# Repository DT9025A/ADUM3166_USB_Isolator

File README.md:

# ADUM3166 USB 隔离器

**该项目使用 Kicad 进行设计，打板请使用附件中的 Gerber 文件或使用 Kicad 工程进行导出。**

使用 IS903 主控的 USB DISK 进行测试，读写速度如下：

采用 5V/5W 的隔离电源，具有较大带负载能力，可以满足一般需求。

Type-C in，USB-A out。

USB 接口处放置了 ESD 二极管 H5VU25U，无需要可不焊接。

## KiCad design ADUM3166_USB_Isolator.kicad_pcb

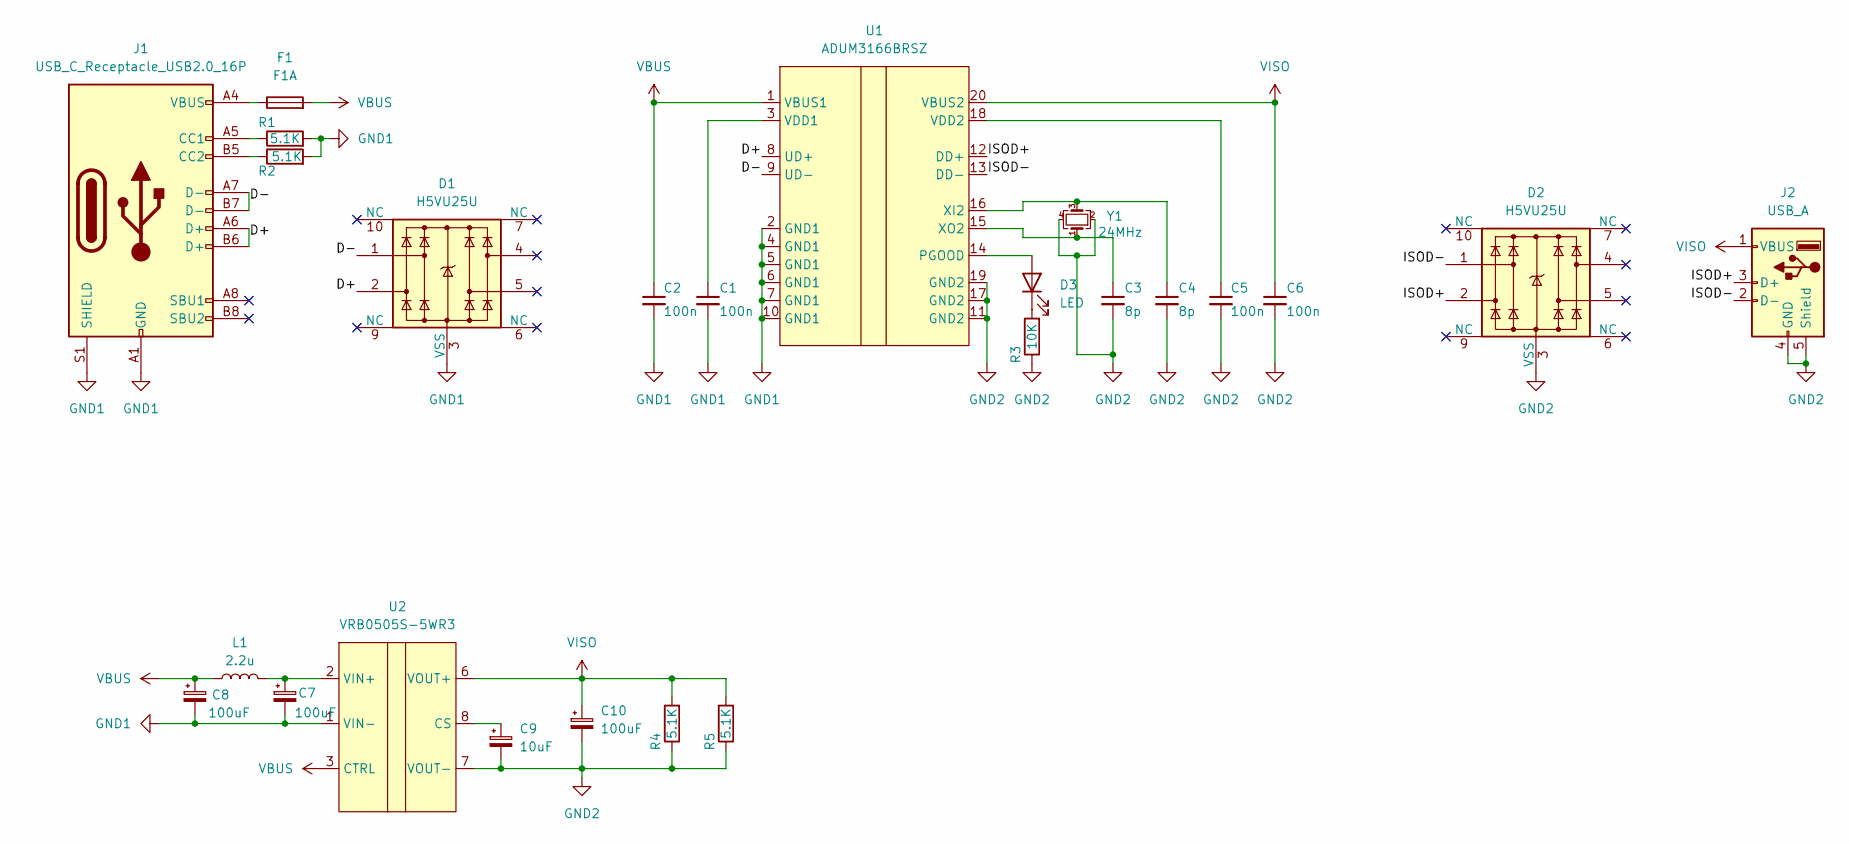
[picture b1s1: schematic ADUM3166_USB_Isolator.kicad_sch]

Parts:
C1, C2, C5, C6: 100n; C_0603_1608Metric_Pad1.08x0.95mm_HandSolder
C3, C4: 8p; C_0402_1005Metric_Pad0.74x0.62mm_HandSolder
C7, C8, C10: 100uF; CP_Elec_6.3x5.4
C9: 10uF; CP_Elec_4x5.4
D1, D2: H5VU25U; Diodes_UDFN-10_1.0x2.5mm_P0.5mm
D3: LED; LED_0603_1608Metric_Pad1.05x0.95mm_HandSolder
F1: F1A; Fuse_1206_3216Metric_Pad1.42x1.75mm_HandSolder
J1: USB_C_Receptacle_USB2.0_16P; USB_C_Receptacle_G-Switch_GT-USB-7010ASV
J2: USB_A; USB_A_CONNFLY_DS1095-WNR0
L1: 2.2u; L_1008_2520Metric_Pad1.43x2.20mm_HandSolder
R1, R2, R4, R5: 5.1K; R_0603_1608Metric_Pad0.98x0.95mm_HandSolder
R3: 10K; R_0603_1608Metric_Pad0.98x0.95mm_HandSolder
U1: ADUM3166BRSZ; SSOP-20_5.3x7.2mm_P0.65mm
U2: VRB0505S-5WR3; VR_S_5W
Y1: 24MHz; Crystal_SMD_2520-4Pin_2.5x2.0mm

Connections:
/D+: D1.2, J1.A6 (D+), J1.B6 (D+), U1.8 (UD+)
/D-: D1.1, J1.A7 (D-), J1.B7 (D-), U1.9 (UD-)
/ISOD+: D2.2, J2.3 (D+), U1.12 (DD+)
/ISOD-: D2.1, J2.2 (D-), U1.13 (DD-)
GND1: C1.2, C2.2, C7.2, C8.2, D1.3 (VSS), D1.8 (VSS), J1.A1 (GND), J1.A12 (GND), J1.B1 (GND), J1.B12 (GND), J1.S1 (SHIELD), R1.2, R2.2, U1.2 (GND1), U1.4 (GND1), U1.5 (GND1), U1.6 (GND1), U1.7 (GND1), U1.10 (GND1), U2.1 (VIN-)
GND2: C3.2, C4.2, C5.2, C6.2, C9.2, C10.2, D2.3 (VSS), D2.8 (VSS), J2.4 (GND), J2.5 (Shield), R3.1, R4.1, R5.1, U1.11 (GND2), U1.17 (GND2), U1.19 (GND2), U2.7 (VOUT-), Y1.2, Y1.4
unnamed: D3.2 (A), U1.14 (PGOOD)
unnamed: D3.1 (K), R3.2
unnamed: F1.1, J1.A4 (VBUS), J1.A9 (VBUS), J1.B4 (VBUS), J1.B9 (VBUS)
unnamed: J1.A5 (CC1), R1.1
unnamed: J1.B5 (CC2), R2.1
unnamed: C1.1, U1.3 (VDD1)
unnamed: C5.1, U1.18 (VDD2)
unnamed: C4.1, U1.16 (XI2), Y1.3
unnamed: C3.1, U1.15 (XO2), Y1.1
unnamed: C9.1, U2.8 (CS)
unnamed: C7.1, L1.2, U2.2 (VIN+)
VBUS: C2.1, C8.1, F1.2, L1.1, U1.1 (VBUS1), U2.3 (CTRL)
VISO: C6.1, C10.1, J2.1 (VBUS), R4.2, R5.2, U1.20 (VBUS2), U2.6 (VOUT+)

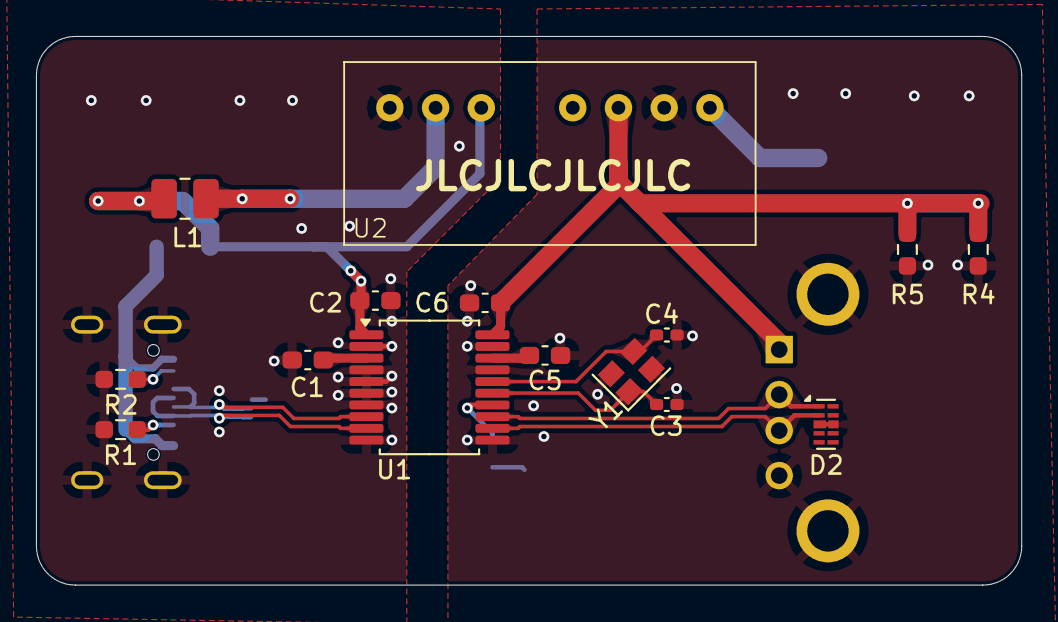
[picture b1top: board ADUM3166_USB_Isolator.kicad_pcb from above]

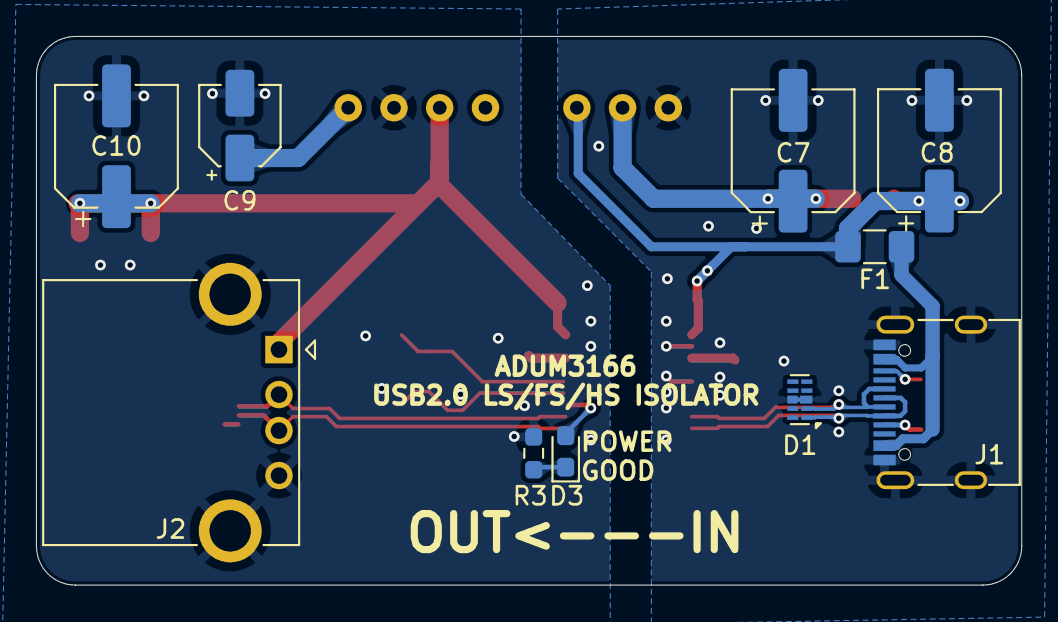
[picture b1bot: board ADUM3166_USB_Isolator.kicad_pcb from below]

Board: 2 copper layers, 54.7 x 30.5 mm, 25 parts (10 on the bottom side), 19 nets.

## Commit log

2025-01-18 上传文件
